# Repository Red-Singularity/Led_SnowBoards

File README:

The goal of this repository is to share code between all members who have custom LED snowbnoards to expedite the process of getting to the slopes
with actually functioning snowboards

This will not only include the code used on the boards but also possible testbeds, images, and other related files
This will be compartmentalized between users as all boards are built differently and require different code
this will allow merges to go a lot smoother since ideally only the user who created the code commited here will be modifying it
This also allows other people to view and test other members code though

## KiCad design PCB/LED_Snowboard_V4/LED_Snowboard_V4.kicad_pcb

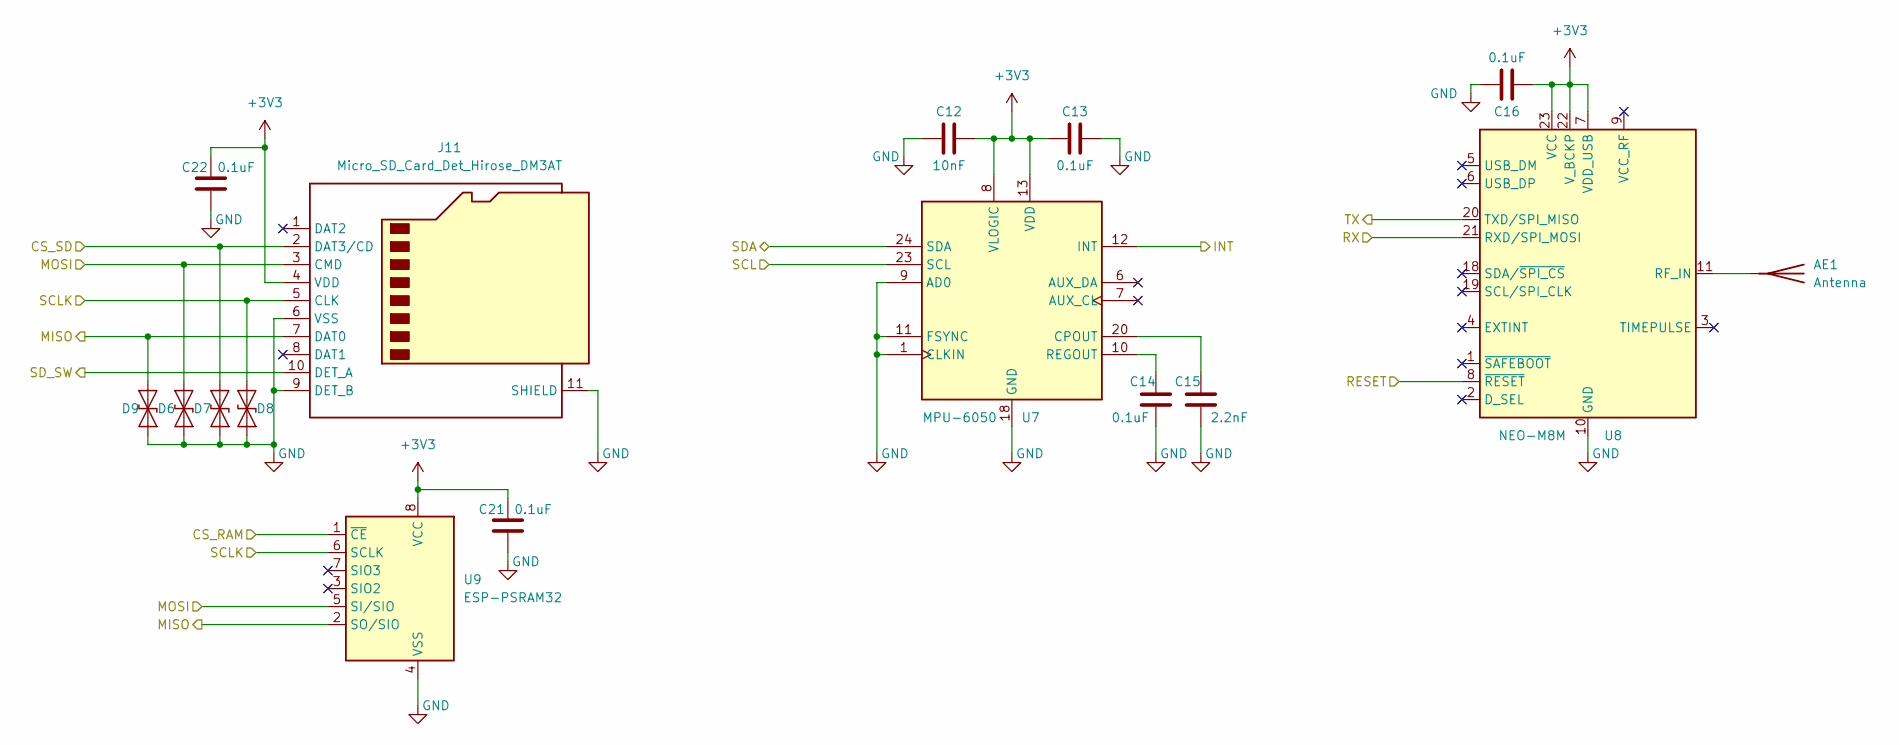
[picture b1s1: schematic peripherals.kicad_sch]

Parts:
AE1: Antenna; U.FL_Hirose_U.FL-R-SMT-1_Vertical
C12: 10nF; C_0603_1608Metric_Pad1.08x0.95mm_HandSolder
C13, C14, C16, C21, C22: 0.1uF; C_0603_1608Metric_Pad1.08x0.95mm_HandSolder
C15: 2.2nF; C_0603_1608Metric_Pad1.08x0.95mm_HandSolder
D6, D7, D8, D9: SD05_SOD323; D_SOD-323
J11: Micro_SD_Card_Det_Hirose_DM3AT; microSD_HC_Hirose_DM3AT-SF-PEJM5
U7: MPU-6050; InvenSense_QFN-24_4x4mm_P0.5mm
U8: NEO-M8M; ublox_NEO
U9: ESP-PSRAM32; SOIC-8_3.9x4.9mm_P1.27mm

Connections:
+3V3: C12.2, C13.1, C16.1, C21.2, C22.2, J11.4 (VDD), U7.8 (VLOGIC), U7.13 (VDD), U8.7 (VDD_USB), U8.22 (V_BCKP), U8.23 (VCC), U9.8 (VCC); also elsewhere on the board
/IO and Power/SCL: U7.23 (SCL); also elsewhere on the board
/IO and Power/SDA: U7.24 (SDA); also elsewhere on the board
/esp32/CS_RAM: U9.1 (~CE); also elsewhere on the board
/esp32/CS_SD: D7.2 (A2), J11.2 (DAT3/CD); also elsewhere on the board
/esp32/INT: U7.12 (INT); also elsewhere on the board
/esp32/MISO: D9.2 (A2), J11.7 (DAT0), U9.2 (SO/SIO); also elsewhere on the board
/esp32/MOSI: D6.2 (A2), J11.3 (CMD), U9.5 (SI/SIO); also elsewhere on the board
/esp32/RESET: U8.8 (~RESET); also elsewhere on the board
/esp32/RX: U8.20 (TXD/SPI_MISO); also elsewhere on the board
/esp32/SCLK: D8.2 (A2), J11.5 (CLK), U9.6 (SCLK); also elsewhere on the board
/esp32/SD_SW: J11.10 (DET_A); also elsewhere on the board
/esp32/TX: U8.21 (RXD/SPI_MOSI); also elsewhere on the board
GND: C12.1, C13.2, C14.1, C15.1, C16.2, C21.1, C22.1, D6.1 (A1), D7.1 (A1), D8.1 (A1), D9.1 (A1), J11.6 (VSS), J11.9 (DET_B), J11.11 (SHIELD), U7.1 (CLKIN), U7.9 (AD0), U7.11 (FSYNC), U7.18 (GND), U8.10 (GND), U8.12 (GND), U8.13 (GND), U8.24 (GND), U9.4 (VSS); also elsewhere on the board
unnamed: AE1.1 (A), U8.11 (RF_IN)
unnamed: C15.2, U7.20 (CPOUT)
unnamed: C14.2, U7.10 (REGOUT)

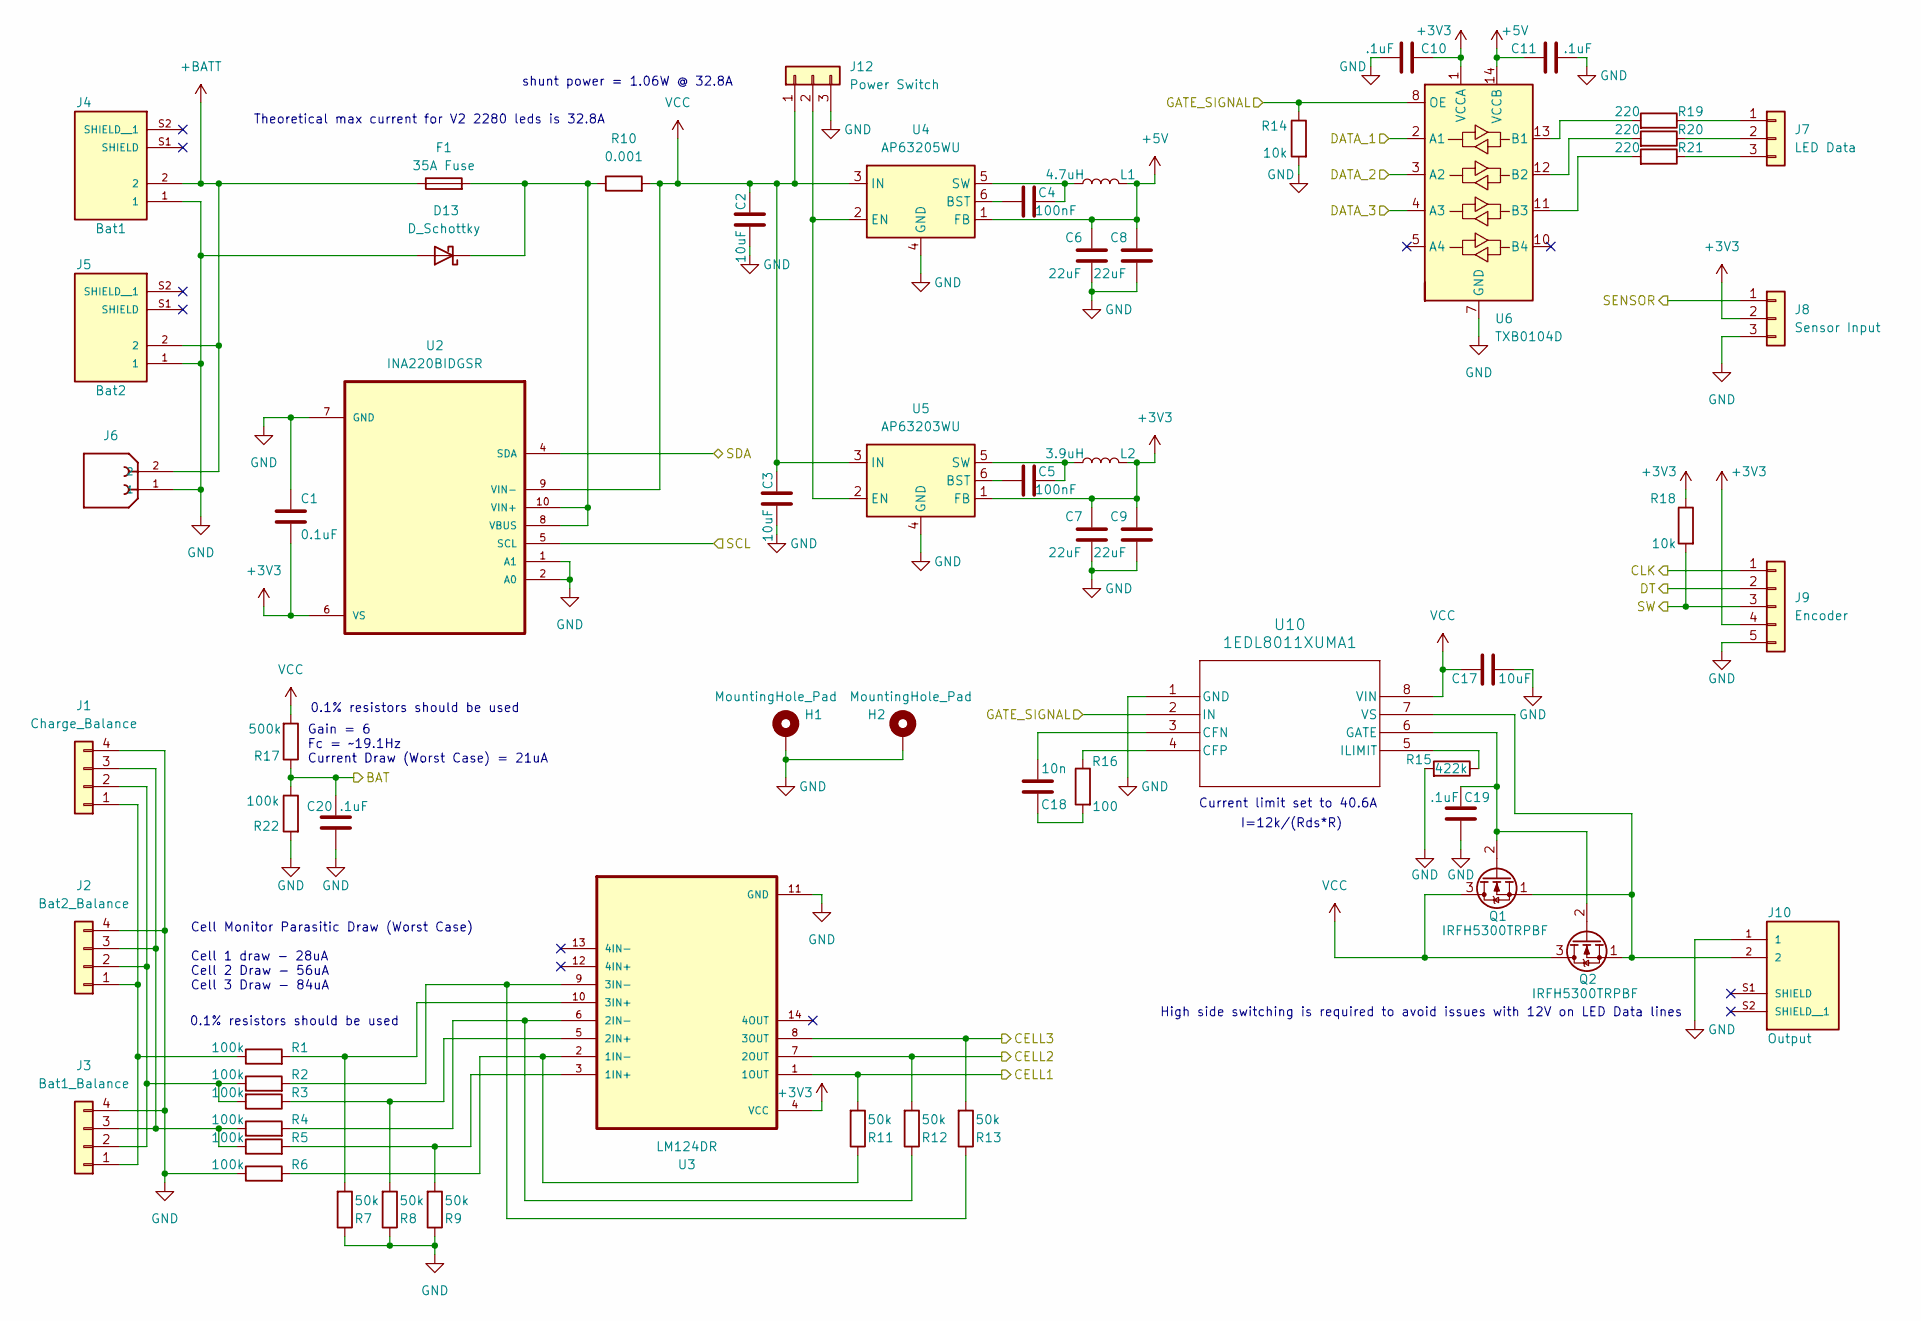
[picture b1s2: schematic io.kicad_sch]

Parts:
C1: 0.1uF; C_0603_1608Metric_Pad1.08x0.95mm_HandSolder
C2, C3, C17: 10uF; C_0603_1608Metric_Pad1.08x0.95mm_HandSolder
C4, C5: 100nF; C_0603_1608Metric_Pad1.08x0.95mm_HandSolder
C6, C7, C8, C9: 22uF; C_0603_1608Metric_Pad1.08x0.95mm_HandSolder
C10, C11, C19, C20: .1uF; C_0603_1608Metric_Pad1.08x0.95mm_HandSolder
C18: 10n; C_0603_1608Metric_Pad1.08x0.95mm_HandSolder
D13: D_Schottky; TO-263-3_TabPin2
F1: 35A Fuse; SF-3812F3500T-2
H1, H2: MountingHole_Pad; MountingHole_4.3mm_M4_Pad
J1: Charge_Balance; JST_XA_B04B-XASK-1_1x04_P2.50mm_Vertical
J2: Bat2_Balance; JST_XA_S04B-XASK-1N-BN_1x04_P2.50mm_Horizontal
J3: Bat1_Balance; JST_XA_S04B-XASK-1N-BN_1x04_P2.50mm_Horizontal
J4: Bat1; AMASS_XT60PW-M_1x02_P7.20mm_Horizontal; PARTREV V1.2
J5: Bat2; AMASS_XT60PW-M_1x02_P7.20mm_Horizontal; PARTREV V1.2
J6: AMASS_XT30U-M_1x02_P5.0mm_Vertical
J7: LED Data; JST_XA_B03B-XASK-1_1x03_P2.50mm_Vertical
J8: Sensor Input; JST_XA_B03B-XASK-1_1x03_P2.50mm_Vertical
J9: Encoder; JST_XA_B05B-XASK-1_1x05_P2.50mm_Vertical
J10: Output; AMASS_XT60PW-F_1x02_P7.20mm_Horizontal; PARTREV V1.2
J12: Power Switch; Molex_Nano-Fit_105309-xx03_1x03_P2.50mm_Vertical
L1: 4.7uH; IND_SRR4818A-150M
L2: 3.9uH; IND_SRR4818A-150M
Q1, Q2: IRFH5300TRPBF; PQFN-8-EP_6x5mm_P1.27mm_Generic
R1, R2, R3, R4, R5, R6, R22: 100k; R_0603_1608Metric_Pad0.98x0.95mm_HandSolder
R7, R8, R9, R11, R12, R13: 50k; R_0603_1608Metric_Pad0.98x0.95mm_HandSolder
R10: 0.001; RES_WSK12161L000FEA
R14, R18: 10k; R_0603_1608Metric_Pad0.98x0.95mm_HandSolder
R15: 422k; R_0603_1608Metric_Pad0.98x0.95mm_HandSolder
R16: 100; R_0603_1608Metric_Pad0.98x0.95mm_HandSolder
R17: 500k; R_0603_1608Metric_Pad0.98x0.95mm_HandSolder
R19, R20, R21: 220; R_0603_1608Metric_Pad0.98x0.95mm_HandSolder
U2: INA220BIDGSR; SOP50P490X110-10N
U3: LM124DR; SOIC127P600X175-14N
U4: AP63205WU; TSOT-23-6
U5: AP63203WU; TSOT-23-6
U6: TXB0104D; SOIC-14_3.9x8.7mm_P1.27mm
U10: 1EDL8011XUMA1; PG-DSO-8-92_INF

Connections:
+3V3: C1.2, C7.2, C9.2, C10.1, J8.2, J9.4, L2.2, R18.1, U2.6 (VS), U3.4 (VCC), U5.1 (FB), U6.1 (VCCA); also elsewhere on the board
+5V: C6.2, C8.2, C11.1, L1.2, U4.1 (FB), U6.14 (VCCB); also elsewhere on the board
+BATT: F1.1, J4.2, J5.2, J6.2; also elsewhere on the board
/IO and Power/BAT: C20.2, R17.1, R22.1; also elsewhere on the board
/IO and Power/CELL1: R11.2, U3.1 (1OUT); also elsewhere on the board
/IO and Power/CELL2: R12.2, U3.7 (2OUT); also elsewhere on the board
/IO and Power/CELL3: R13.2, U3.8 (3OUT); also elsewhere on the board
/IO and Power/CLK: J9.1; also elsewhere on the board
/IO and Power/DATA_1: U6.2 (A1); also elsewhere on the board
/IO and Power/DATA_2: U6.3 (A2); also elsewhere on the board
/IO and Power/DATA_3: U6.4 (A3); also elsewhere on the board
/IO and Power/DT: J9.2; also elsewhere on the board
/IO and Power/GATE_SIGNAL: R14.1, U6.8 (OE), U10.2 (IN); also elsewhere on the board
/IO and Power/SCL: U2.5 (SCL); also elsewhere on the board
/IO and Power/SDA: U2.4 (SDA); also elsewhere on the board
/IO and Power/SENSOR: J8.1; also elsewhere on the board
/IO and Power/SW: J9.3, R18.2; also elsewhere on the board
GND: C1.1, C2.1, C3.1, C6.1, C7.1, C8.1, C9.1, C10.2, C11.2, C17.1, C19.1, C20.1, D13.3 (A), H1.1, H2.1, J1.4, J2.4, J3.4, J4.1, J5.1, J6.1, J8.3, J9.5, J10.1, J12.3, R6.1, R7.1, R8.1, R9.1, R14.2, R15.2, R22.2, U2.1 (A1), U2.2 (A0), U2.7 (GND), U3.11 (GND), U4.4 (GND), U5.4 (GND), U6.7 (GND), U10.1 (GND); also elsewhere on the board
unnamed: C18.2, R16.2
unnamed: D13.2 (K), F1.2, R10.2, U2.8 (VBUS), U2.10 (VIN+)
unnamed: J1.1, J2.1, J3.1, R1.1
unnamed: J1.2, J2.2, J3.2, R2.1, R3.2
unnamed: J1.3, J2.3, J3.3, R4.1, R5.1
unnamed: J7.1, R19.1
unnamed: J7.2, R20.1
unnamed: J7.3, R21.1
unnamed: J12.2, U4.2 (EN), U5.2 (EN)
unnamed: C19.2, Q1.2 (G), Q2.2 (G), U10.6 (GATE)
unnamed: J10.2, Q1.1 (S), Q2.1 (S), U10.7 (VS)
unnamed: R5.2, R9.2, U3.3 (1IN+)
unnamed: R6.2, R11.1, U3.2 (1IN-)
unnamed: R3.1, R8.2, U3.5 (2IN+)
unnamed: R4.2, R12.1, U3.6 (2IN-)
unnamed: R1.2, R7.2, U3.10 (3IN+)
unnamed: R2.2, R13.1, U3.9 (3IN-)
unnamed: C4.1, U4.6 (BST)
unnamed: C4.2, L1.1, U4.5 (SW)
unnamed: C5.1, U5.6 (BST)
unnamed: C5.2, L2.1, U5.5 (SW)
unnamed: R19.2, U6.13 (B1)
unnamed: R20.2, U6.12 (B2)
unnamed: R21.2, U6.11 (B3)
unnamed: C18.1, U10.3 (CFN)
unnamed: R16.1, U10.4 (CFP)
unnamed: R15.1, U10.5 (ILIMIT)
VCC: C2.2, C3.2, C17.2, J12.1, Q1.3 (D), Q2.3 (D), R10.3, R17.2, U2.9 (VIN-), U4.3 (IN), U5.3 (IN), U10.8 (VIN); also elsewhere on the board

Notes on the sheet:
Current limit set to 40.6A
Gain = 6 Fc = ~19.1Hz Current Draw (Worst Case) = 21uA
Cell Monitor Parasitic Draw (Worst Case) Cell 1 draw - 28uA Cell 2 Draw - 56uA Cell 3 Draw - 84uA
I=12k/(Rds*R)
Theoretical max current for V2 2280 leds is 32.8A
High side switching is required to avoid issues with 12V on LED Data lines
0.1% resistors should be used
shunt power = 1.06W @ 32.8A

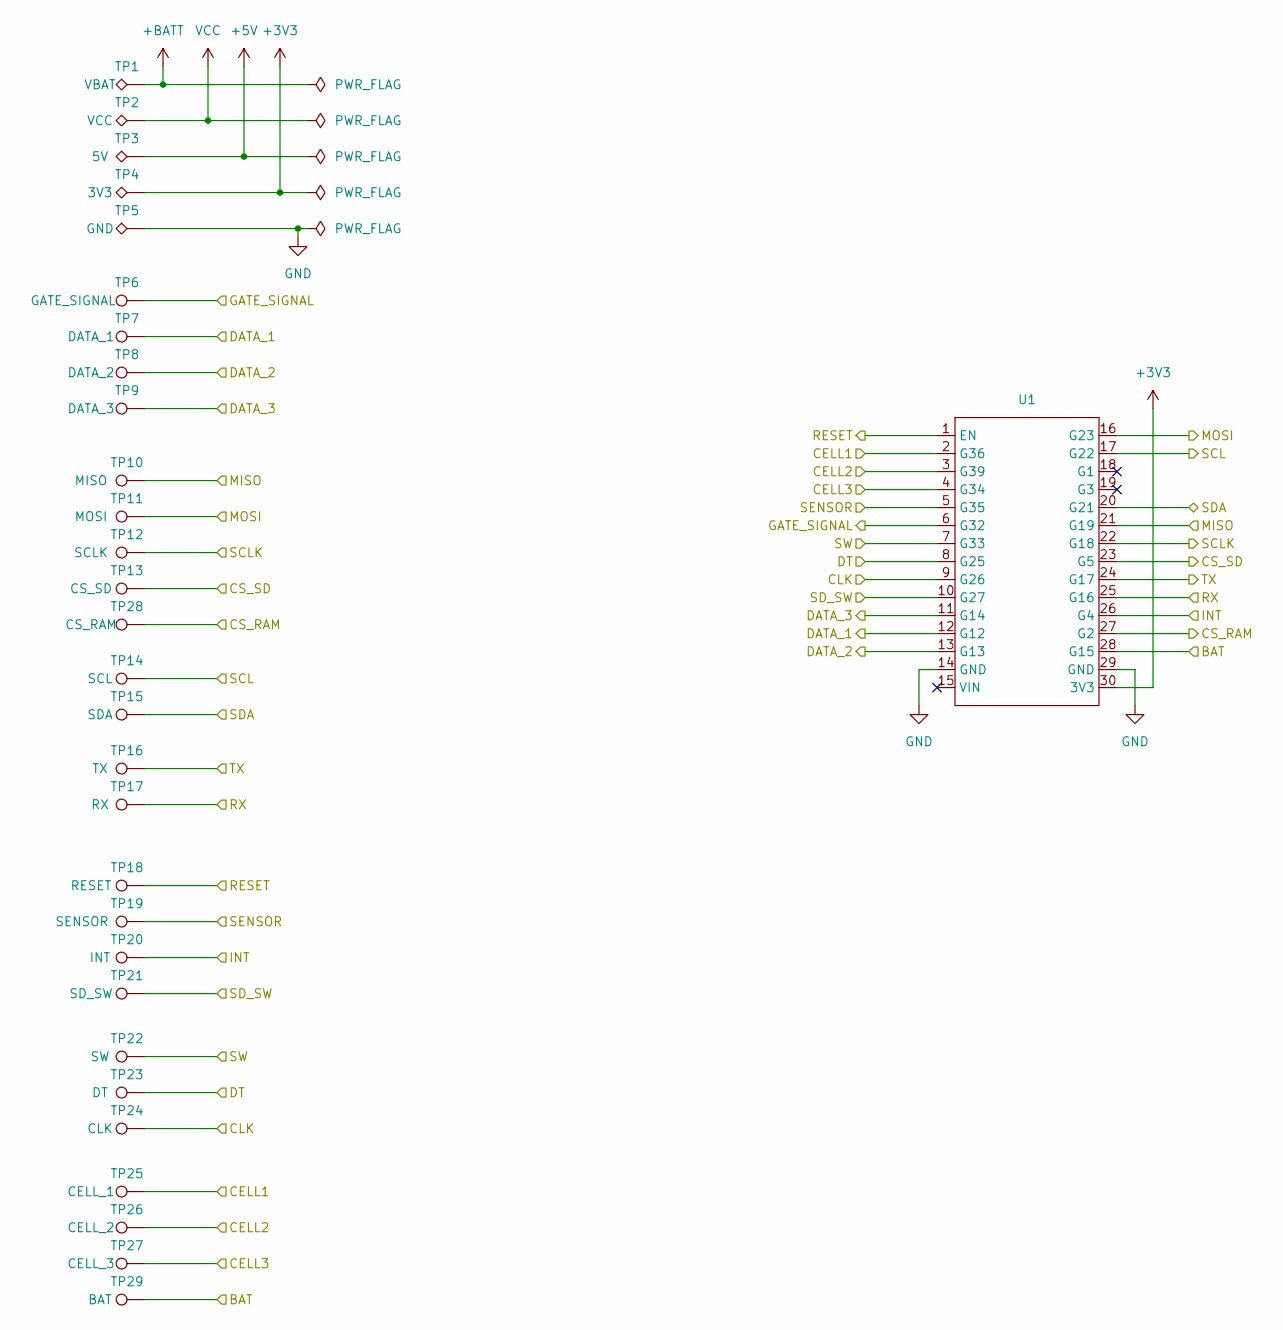
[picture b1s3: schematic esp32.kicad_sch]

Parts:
TP1: VBAT; TestPoint_Pad_3.0x3.0mm
TP2: VCC; TestPoint_Pad_3.0x3.0mm
TP3: 5V; TestPoint_Pad_3.0x3.0mm
TP4: 3V3; TestPoint_Pad_3.0x3.0mm
TP5: GND; TestPoint_Pad_3.0x3.0mm
TP6: GATE_SIGNAL; TestPoint_Pad_D1.5mm
TP7: DATA_1; TestPoint_Pad_D1.5mm
TP8: DATA_2; TestPoint_Pad_D1.5mm
TP9: DATA_3; TestPoint_Pad_D1.5mm
TP10: MISO; TestPoint_Pad_D1.5mm
TP11: MOSI; TestPoint_Pad_D1.5mm
TP12: SCLK; TestPoint_Pad_D1.5mm
TP13: CS_SD; TestPoint_Pad_D1.5mm
TP14: SCL; TestPoint_Pad_D1.5mm
TP15: SDA; TestPoint_Pad_D1.5mm
TP16: TX; TestPoint_Pad_D1.5mm
TP17: RX; TestPoint_Pad_D1.5mm
TP18: RESET; TestPoint_Pad_D1.5mm
TP19: SENSOR; TestPoint_Pad_D1.5mm
TP20: INT; TestPoint_Pad_D1.5mm
TP21: SD_SW; TestPoint_Pad_D1.5mm
TP22: SW; TestPoint_Pad_D1.5mm
TP23: DT; TestPoint_Pad_D1.5mm
TP24: CLK; TestPoint_Pad_D1.5mm
TP25: CELL_1; TestPoint_Pad_D1.5mm
TP26: CELL_2; TestPoint_Pad_D1.5mm
TP27: CELL_3; TestPoint_Pad_D1.5mm
TP28: CS_RAM; TestPoint_Pad_D1.5mm
TP29: BAT; TestPoint_Pad_D1.5mm
U1: MODULE_ESP32_DEVKIT_V1

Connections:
+3V3: TP4.1, U1.30 (3V3); also elsewhere on the board
+5V: TP3.1; also elsewhere on the board
+BATT: TP1.1; also elsewhere on the board
/IO and Power/BAT: TP29.1, U1.28 (G15); also elsewhere on the board
/IO and Power/CELL1: TP25.1, U1.2 (G36); also elsewhere on the board
/IO and Power/CELL2: TP26.1, U1.3 (G39); also elsewhere on the board
/IO and Power/CELL3: TP27.1, U1.4 (G34); also elsewhere on the board
/IO and Power/CLK: TP24.1, U1.9 (G26); also elsewhere on the board
/IO and Power/DATA_1: TP7.1, U1.12 (G12); also elsewhere on the board
/IO and Power/DATA_2: TP8.1, U1.13 (G13); also elsewhere on the board
/IO and Power/DATA_3: TP9.1, U1.11 (G14); also elsewhere on the board
/IO and Power/DT: TP23.1, U1.8 (G25); also elsewhere on the board
/IO and Power/GATE_SIGNAL: TP6.1, U1.6 (G32); also elsewhere on the board
/IO and Power/SCL: TP14.1, U1.17 (G22); also elsewhere on the board
/IO and Power/SDA: TP15.1, U1.20 (G21); also elsewhere on the board
/IO and Power/SENSOR: TP19.1, U1.5 (G35); also elsewhere on the board
/IO and Power/SW: TP22.1, U1.7 (G33); also elsewhere on the board
/esp32/CS_RAM: TP28.1, U1.27 (G2); also elsewhere on the board
/esp32/CS_SD: TP13.1, U1.23 (G5); also elsewhere on the board
/esp32/INT: TP20.1, U1.26 (G4); also elsewhere on the board
/esp32/MISO: TP10.1, U1.21 (G19); also elsewhere on the board
/esp32/MOSI: TP11.1, U1.16 (G23); also elsewhere on the board
/esp32/RESET: TP18.1, U1.1 (EN); also elsewhere on the board
/esp32/RX: TP17.1, U1.25 (G16); also elsewhere on the board
/esp32/SCLK: TP12.1, U1.22 (G18); also elsewhere on the board
/esp32/SD_SW: TP21.1, U1.10 (G27); also elsewhere on the board
/esp32/TX: TP16.1, U1.24 (G17); also elsewhere on the board
GND: TP5.1, U1.14 (GND), U1.29 (GND); also elsewhere on the board
VCC: TP2.1; also elsewhere on the board

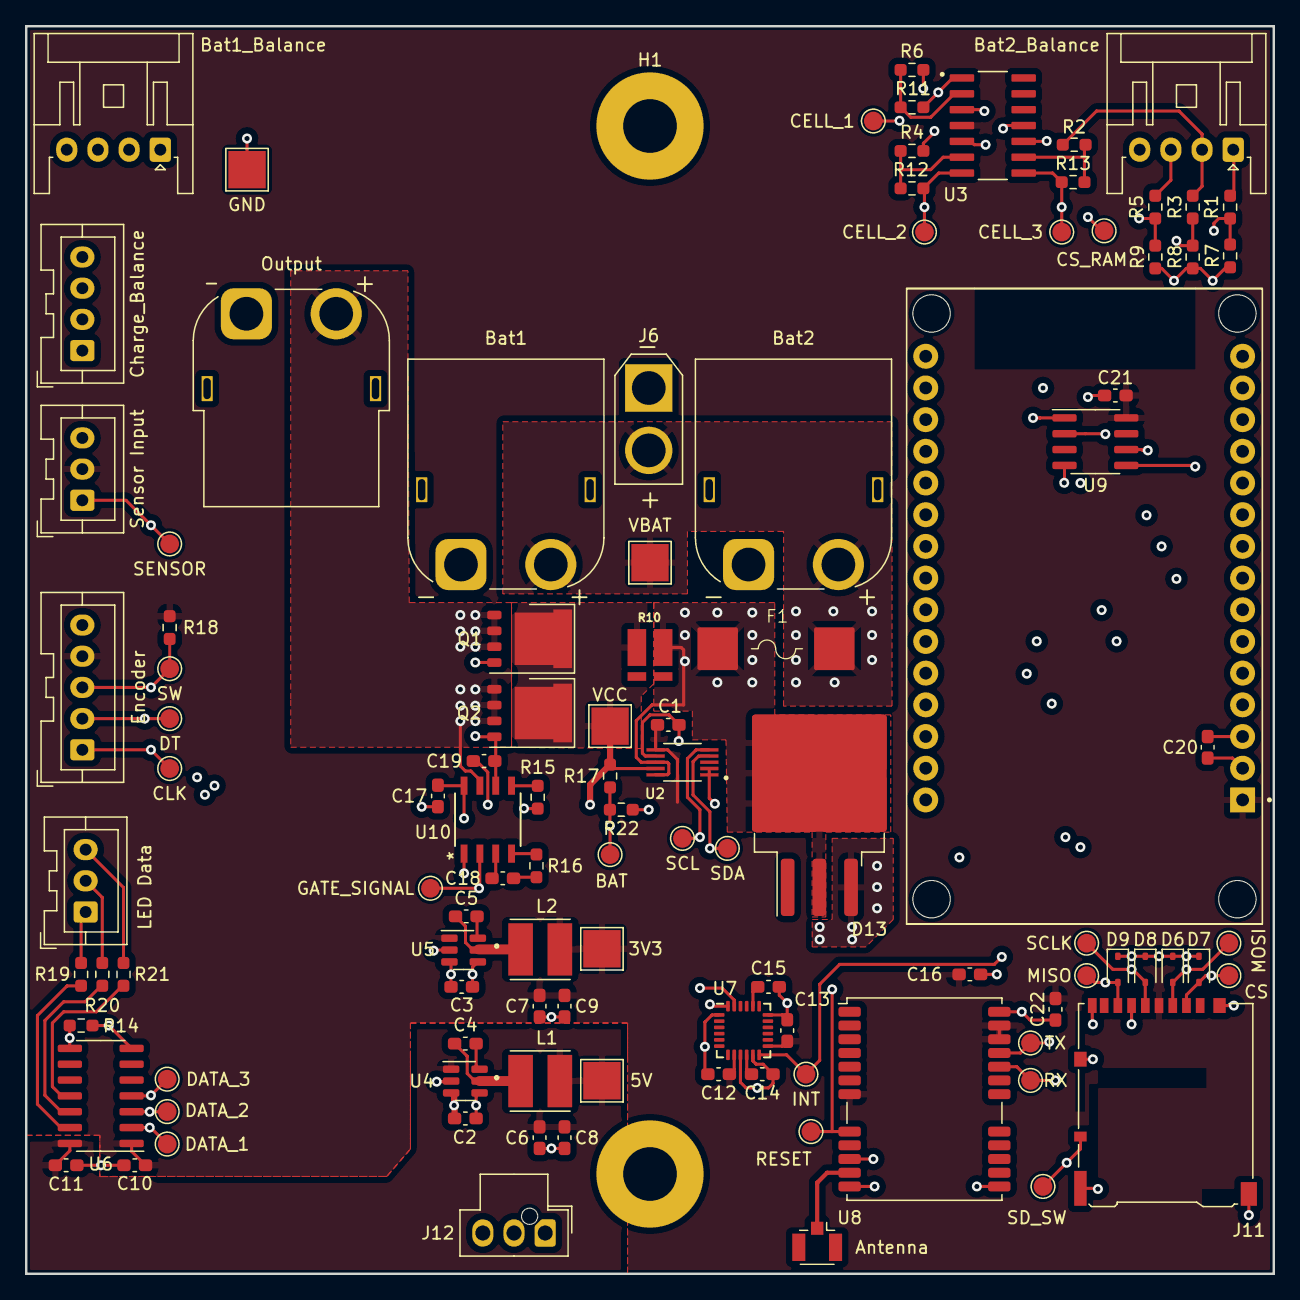
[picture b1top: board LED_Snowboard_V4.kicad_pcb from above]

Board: 4 copper layers, 100.0 x 100.0 mm, 108 parts (0 on the bottom side), 59 nets.

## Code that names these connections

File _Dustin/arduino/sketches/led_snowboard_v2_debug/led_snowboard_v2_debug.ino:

/*
Dustin Fisher

Test code for the led matrix snowboard based on led_snowboard_v2
*/

#include "SdFat.h" // interfaces with sd card
#include "sdios.h" // sd card comms
#include "SPI.h" // handles SPI comms
//#include "BluetoothSerial.h" // Bluetooth comms
#include <Wire.h> // i2c communication
//#include <INA220.h> // for power monitor https://github.com/nathancheek/INA220
#include <FastLED.h> // main led control

//pin defines
#define CELL_1 36 // analog cell 1 data
#define CELL_2 39 // analog cell 2 data
#define CELL_3 34 // analog cell 3 data
#define SENSOR 35 // analog read sensor data
#define GATE_SIGNAL 32 //controls the mosfet for led strip power
#define SW 33 // Encoder switch
#define DT 25 // Encoder DT pin
#define CLK 26 // Encoder clock pin
#define SD_SW 27 // SD detect switch
#define DATA_3 14 // sets pin data is being sent from
#define DATA_1 12 // sets pin data is being sent from
#define DATA_2 13 // sets pin data is being sent from
#define MOSI 23 // MOSI SPI pin
#define SCL 22 // I2C clock pin
#define SDA 21 // I2C data pin
#define MISO 19 // MISO SPI pin
#define SCLK 18 // SPI clock pin
#define SD_CS_PIN 5 // SD card chip select
#define TX 17 // UART transmit pin
#define RX 16 // UART receive pin
#define INT 26 // mpu6050 interrupt
#define CS_RAM 2 // PSRAM chip select
#define BAT 15 // battery voltage voltage divider

//other defines
#define NUM_LEDS 2090 //2090 sets the amount of pixels being controlled
#define TOP_LEDS 60
#define MPU_addr 0x68 //i2c address of mpu
//setting for mpu degrees per second
#define dps2000 0x18
#define dps1000 0x10
#define dps500 0x08
#define dps250 0x00
//setting for mpu degrees per second
#define g16 0x18
#define g8 0x10
#define g4 0x08
#define g2 0x00

//spi speed
#define SPI_CLOCK SD_SCK_MHZ(20)

// Try to select the best SD card configuration.
#if HAS_SDIO_CLASS
#define SD_CONFIG SdioConfig(FIFO_SDIO)
#elif  ENABLE_DEDICATED_SPI
#define SD_CONFIG SdSpiConfig(SD_CS_PIN, DEDICATED_SPI, SPI_CLOCK)
#else  // HAS_SDIO_CLASS
#define SD_CONFIG SdSpiConfig(SD_CS_PIN, SHARED_SPI, SPI_CLOCK)
#endif  // HAS_SDIO_CLASS

//initialize BluetoothSerial class as SerialBT
//BluetoothSerial SerialBT;

//INA220 library initialization as ina220
//INA220 ina220;

//initialize sd card class as sd
SdFat SD;

//initialize File class as file
File file;

//initialize led strips
CRGB half1[NUM_LEDS/2];
CRGB half2[NUM_LEDS/2];
CRGB top[TOP_LEDS];

//Global variables
int frameData[NUM_LEDS]; // array of data for single frame
int cal = 50; // amount of loops to get gyro data for calibration
int offsetx, offsety, offsetz; // offset values for gyro
int counter = 0; // generic counter for testing
int frame_number = 0; // sets the frame being displayed for the current gif

const uint8_t NUM_INA = 1; // 2 INA devices
const uint8_t MAX_CUR = 40; // 5 Amps
const uint16_t SHUNT_R = 1000; // 1 mOhm

uint8_t ina_addresses[NUM_INA] = {0x40}; // INA I2C addresses

bool bat_safe = 0; //flag for enabling or disabling low battery cutoff. 1 = safety enabled
bool rand_LED = 0; // flag for random sequence animation
bool nyan = 0; // flag for setting nyan cat animation
bool freefall = 0; // flag for freefall detection
bool pacman = 0;
bool kirby = 0;
bool mario = 0;
bool neon = 0;

float ax, ay, az; // accelerometer data in Gs
float gx, gy, gz; // gyro data in degrees/second
float comp_x, comp_y = 0; // complimentary filter angles
float gyro_angle_x, gyro_angle_y, gyro_angle_z = 0; // angle calculated with gyro
float temp_c; // temperature sensor on mpu. in degrees c
float mpu_timer = 0; // timer to get data from gyro in mpu
float voltage, current, power; // ina chip values
float timer = 0; // generic timer
float minCell = 4.2; // minimum cell voltage reading

String accel_set = "16g"; // 2g, 4g, 8g, 16g
String gyro_set = "2000dps"; // 250dps, 500dps, 1000dps, 2000dps

void setup() {
  //setup serial output
  Serial.begin(115200);

  //set pin modes
  pinMode(DATA_1, OUTPUT); // set led data pins to output
  pinMode(DATA_2, OUTPUT); 
  pinMode(DATA_3, OUTPUT);
  pinMode(GATE_SIGNAL, OUTPUT); // turns on 12v to leds
  pinMode(BAT, INPUT);

  //device setups
  //INA_setup(); //INA220 setup
  sd_setup(); //setup sd card
  //bluetooth_setup(); //setup bluetooth
  
  //setup led strips
  digitalWrite(GATE_SIGNAL, true);
  FastLED.addLeds<WS2812, DATA_1, BGR>(half1, NUM_LEDS);
  FastLED.addLeds<WS2812, DATA_2, BGR>(half2, NUM_LEDS);
  FastLED.addLeds<WS2812, DATA_3, BGR>(top, TOP_LEDS);
  FastLED.setCorrection(TypicalLEDStrip);
  //set brightness to 5%
  FastLED.setBrightness(5);
  FastLED.show();
  
}

void loop() {
  timer = millis();

  //getInaValues(); //get board status (battery info, current measurements, etc)
  //getBatteryData(); // get all battery data
  //bluetooth_control(); // use data over bluetooth to control images

  //for(int i=0; i<(NUM_LEDS/2); i++){
      //half1[i] = random(0, 0xFFFFFF);
      //half2[i+1] = random(0, 0xFFFFFF);
    //}

  //get MPU data
  //get GPS data
  //app();
  //get gps data

  Serial.print("loop() running on core "); Serial.println(xPortGetCoreID());

  assign_pacman();

  FastLED.show();

  //Serial.println(millis()-timer);
}


Void Task1code( void * parameter) {
  for(;;) {
    Code for task 1 - infinite loop
    (...)
  }
}

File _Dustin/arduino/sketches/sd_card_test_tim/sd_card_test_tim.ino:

//Define compile debug variables:
#define RAM_DEBUG true

//Include libraries to handle peripherals:
#include <SPI.h>

//Define pins on the left side (EN button side) of ESP32:
#define CELL1         36
#define CELL2         39
#define CELL3         34
#define ANALOG_SENSOR 35
#define GATE          32
#define ENCODER_SW    33
#define ENCODER_DT    25
#define ENCODER_CLK   26
#define SD_SW         27
#define LED3          14
#define LED1          12
#define LED2          13

//Define pins on the right side (BOOT button side) of ESP32:
#define MOSI    23
#define SCL     22
#define SDA     21
#define MISO    19
#define SCLK    18
#define CS_SD   5
#define TX      17
#define RX      16
#define INT     4
#define CS_RAM  2

//RAM setup:
SPISettings RAM_SETTINGS(1000000,MSBFIRST,SPI_MODE1);

void setup(){
  Serial.begin(115200);
  while(!Serial){}
  pinMode(CS_RAM,OUTPUT);
  pinMode(CS_SD,OUTPUT);
  digitalWrite(CS_RAM,HIGH);
  digitalWrite(CS_SD,HIGH);
  SPI.begin();
}

uint8_t write_buff[] = {0x02, 0x00, 0x00, 0x00, 0x69};

void loop(){
  //write
  digitalWrite(CS_RAM,LOW);
  SPI.beginTransaction(RAM_SETTINGS);
  SPI.transfer(write_buff, sizeof(write_buff));
  SPI.endTransaction();
  digitalWrite(CS_RAM,HIGH);

  delay(500);

  //read
  uint8_t read_buff[] = {0x03, 0x00, 0x00, 0x00, 0xFF};
  uint8_t read_buff_size = sizeof(read_buff);
  digitalWrite(CS_RAM,LOW);
  SPI.beginTransaction(RAM_SETTINGS);
  SPI.transfer(read_buff,read_buff_size);
  SPI.endTransaction();
  Serial.print("DATA: "); Serial.println(read_buff[4]);
  digitalWrite(CS_RAM,HIGH);
  delay(500);
}

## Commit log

2022-10-10 Create README
    initial commit
2022-10-10 Added folder structure
    Added initial folder structure. needed to add junk files to properly commit as I could not add empty folders
2022-10-11 added pcb files
    added easy eda pcb files as zip
2022-10-13 getting started
    got PIL and vs code working and used a demo to display an image the size of the snowboard
2022-10-15 Determined Input File Style
    Determined that I will use two separate .dat files as inputs for the simulator. Created a python file that outputs a single dimensional array to dat files in proper format. Also made concatanation fu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
2022-10-16 Figured out how to transfer data from non standard array to image
    Using the addition of a couple new functions I was able to create generic functions that can write either the data needed or a 0 depending on how the snowboard is laid out. In order to test I need to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
2022-10-20 Fixed array size issue
    fixed issue with array sizes stemming from improper tracking of place in row where data is assigned. need to fix split section of board and create a fade pattern for testing
2022-10-21 Possible fixed image display
    added a flip variable to indicate how data is being assigned to a given row. also incorporated simple red gradient test which shows promise
2022-10-22 Working Sim!
    supposedly fully working simulator. uses fading rgb values to confirm led strip direction and shape
2022-10-22 deleted useless comments and used nearest neighbor filter
2022-10-23 started image translator
    started python file that converts images into single dimensional array the board can read
2022-10-26 Almost have image translator working
    Just about finished the image translator. there is a weird pixel shifting error on the second side of the board. Its unclear if this is a fault of the simulator or the image translator
2022-10-27 Initial working image translator
    got the image translator working in its most basic form. this can now easily be used in conjunction with the simulator
2022-10-28 added image_positioning function
    added image positioning function which centers image on the board. Also added capability to adjust background color in the simulator
2022-10-30 Fixed row20 backwards issue
    fixed issue where the 20th row was improperly indexing and showing incorrect values.
2022-11-07 Started arduino test code
    started basic tests with arduino to read data from sd card
2022-11-13 Ability to read files to array
    started main snowboard code and determined how to read files to an array at variable speeds up to 50mhz on spi
2022-11-18 added mpu functions
    created functions to set parameters and get data from mpu6050. this includes all axis for gyro and accel, calibration function for gyro, and getting temperature readings
2022-11-20 mpu functions and start of app
    Finished basic functions to get angles from mpu. started basic bluetooth communication and setup. also began making directory and workspace for bluetooth app
2023-01-26 Desktop -> Laptop
    doing some basic tests on the snowboard
2023-01-27 Tremblant trip
    added basic bluetooth control for colors, rand function and brightness as well as battery low voltage cutoff
2023-01-31 nyan prep
    prepped arduino code to test nyan cat image. also re simulated nyan cat and made custom folder to hold data.
2023-01-31 successful nyan cat
    created a gif of nyan cat that is displayed properly on the board
2023-02-04 laptop commit
2023-02-28 added pacman gif
    added pacman gifs to media file and ran through sim and translator. also fixed issue with each image preview keeps popping up in translator
2023-02-28 started on the header creator
2023-02-28 fixing git
2023-03-02 header creator works
    got the header creator to work
2023-03-03 fixed small issues
    fixed small issues in arduino code and simulator.
2023-04-28 added led snowboard v1
    added old sketches for v1 to repository
2023-10-19 Moved to Kicad
    created replica of pcb schematic in kicad and started work on app again
2023-10-19 Transfer PCB To Desktop
2023-10-21 Post Review
    Reviewed with Tim. need to add power line protections. settled on no battery heater for now
2023-10-24 pcb transfer to laptop
2023-11-18 makerfaire
2023-11-29 trasnsfer
2023-11-30 routed all main lines and added power vias
2023-11-30 main routing complete v4
2023-12-04 Added all smd footprints
    just need to add jst connectors and change gps antennae
2023-12-05 impedance matched antennae
2023-12-05 finished v4 design before review
2023-12-07 Added Ram
    Added Ram. need to finish DRC checks
2023-12-11 Finished PCB with all feedback
2023-12-22 Updated Arduino Code
    updated arduino code for use with V4 board and added some test scripts. also got the board to work with SD card
2024-01-02 github update
    just syncing files
2024-01-04 Fixed frame read issues
    fixed issue where setting sd card read would freeze all commands. also added op amp readings.
2024-01-07 arduino tweaks and pcb notes
2024-02-10 android studio tests
    finally got a bottom navigation to kinda work
2024-02-12 got bottom nav to actually work this time
2024-02-12 file management
2024-09-01 Create test
2024-09-01 quick sync
    quick sync
2024-10-13 Center Flex Fixes
    fixed board outline to matrix misalignment issue and added extra pads for pass through from tiling board
2024-11-21 Flex PCBs ordered
    All Flex PCBs are finalized and ordered
2024-12-15 ws2816 tests
    started initial ws2816 tests
2025-07-02 updated control pcb
    updated to add high side switching as well as added voltage divider and adjusted layout
2025-07-13 oredered board
2025-07-17 confirmed working code before opensauce
    confirmed the image translator and simulator works before open sauce. also verified all arduino code works but could use debugging on V2 to fix glitching
2025-07-17 transfer to laplet
2025-07-18 ready for open sauce
    all code working and ready for the event
2026-04-14 working clock mode
2026-04-15 finished clock mode for V1
